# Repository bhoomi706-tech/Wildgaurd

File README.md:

# 🌿 WildGuard IoT System

## 🚀 Overview
WildGuard is an IoT-based smart wildlife monitoring and protection system designed to prevent human-animal conflicts and ensure real-time tracking and surveillance.

---

## 🧠 Features
- 📍 GPS Tracking for location monitoring
- 🎥 ESP32-CAM for live video feed
- 🔴 IR Sensors for obstacle/animal detection
- 📡 RFID for identification
- 🚗 Motor Control using TB6612 Driver
- ⚡ Efficient Power Management (12V → 5V → 3.3V)

---

## 🧩 Components Used
- ESP32
- ESP32-CAM
- Neo-6M GPS Module
- RFID RC522
- IR Sensors
- TB6612 Motor Driver
- 12V DC Motors
- Buck Converter (LM2596)
- AMS1117 Voltage Regulator

---

## 🔌 System Architecture
- 12V supply powers motors
- Buck converter steps down to 5V
- AMS1117 regulates 3.3V for ESP32 and sensors
- ESP32 acts as the main controller

---

## 🛠️ Technologies
- Embedded Systems
- IoT
- PCB Design (KiCad)
- Wireless Communication

---

## 📂 Project Structure

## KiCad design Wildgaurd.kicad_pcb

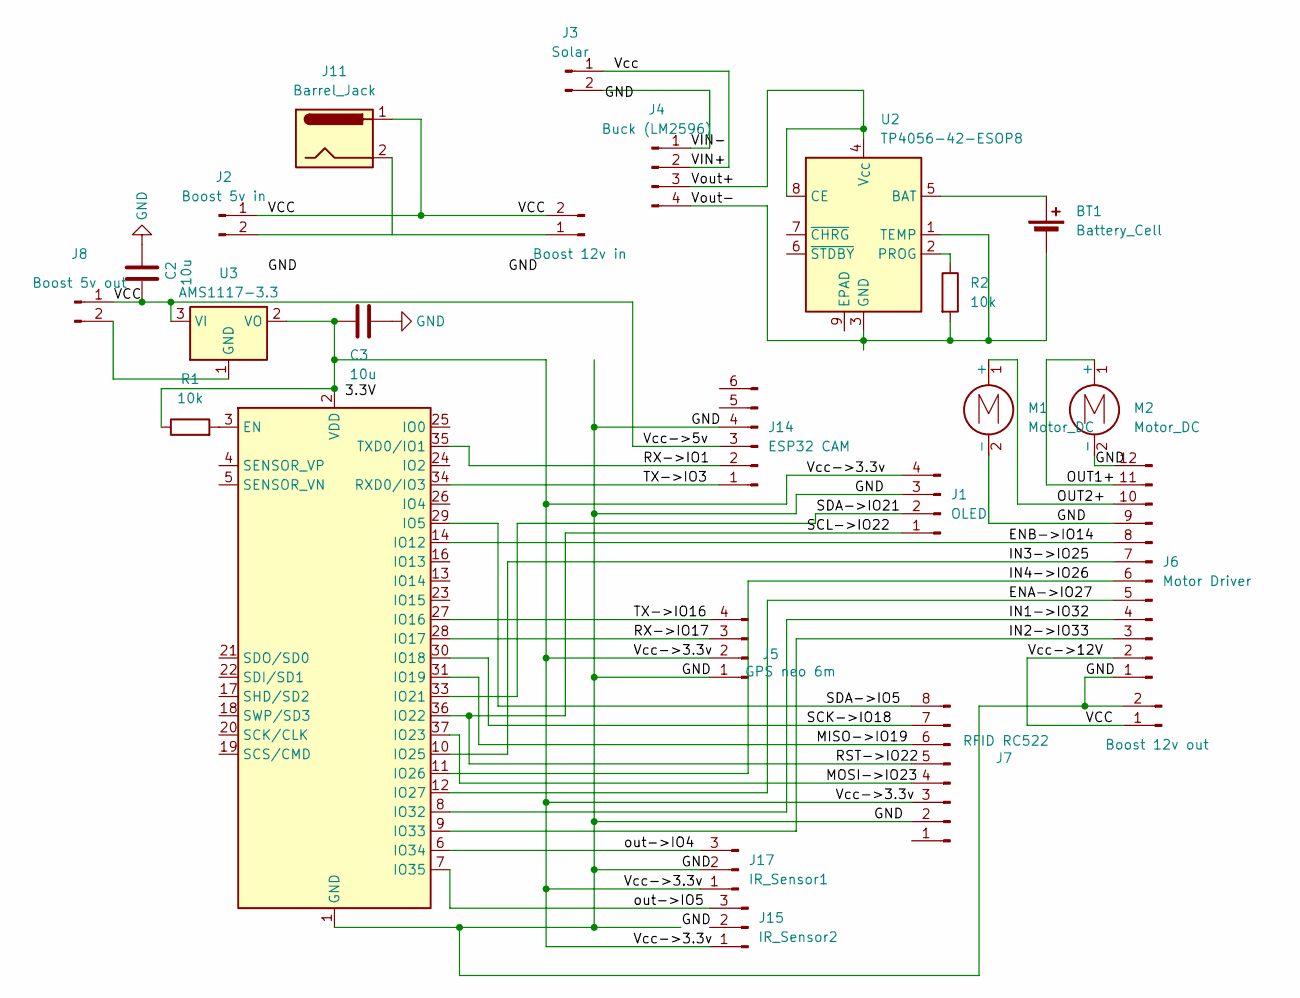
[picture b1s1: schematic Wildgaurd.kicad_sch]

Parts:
BT1: Battery_Cell; BatteryHolder_Keystone_1042_1x18650
C2, C3: 10u; C_0805_2012Metric
J1: OLED; PinHeader_1x04_P2.54mm_Vertical
J2: Boost 5v in; PinHeader_1x02_P2.54mm_Vertical
J3: Solar; PinHeader_1x02_P2.54mm_Vertical
J4: Buck (LM2596); PinHeader_1x04_P2.54mm_Vertical
J5: GPS neo 6m; PinHeader_1x04_P2.54mm_Vertical
J6: Motor Driver; PinHeader_1x12_P2.54mm_Vertical
J7: RFID RC522; PinHeader_1x08_P2.54mm_Vertical
J8: Boost 5v out; PinHeader_1x02_P2.54mm_Vertical
J9: Boost 12v in; PinHeader_1x02_P2.54mm_Vertical
J10: Boost 12v out; PinHeader_1x02_P2.54mm_Vertical
J11: Barrel_Jack; BarrelJack_Horizontal
J14: ESP32 CAM; PinHeader_1x06_P2.54mm_Vertical
J15: IR_Sensor2; PinHeader_1x03_P2.54mm_Vertical
J17: IR_Sensor1; PinHeader_1x03_P2.54mm_Vertical
M1, M2: Motor_DC; TerminalBlock_MaiXu_MX126-5.0-02P_1x02_P5.00mm
R1, R2: 10k; R_0815_2038Metric
U1: ESP32-WROOM-32
U2: TP4056-42-ESOP8; SOIC-8-1EP_3.9x4.9mm_P1.27mm_EP2.41x3.3mm_ThermalVias
U3: AMS1117-3.3; SOT-223-3_TabPin2

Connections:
/ENA->IO27: J6.5, U1.12 (IO27)
/ENB->IO14: J6.8, U1.14 (IO12)
/IN1->IO32: J6.4, U1.8 (IO32)
/IN2->IO33: J6.3, U1.9 (IO33)
/IN3->IO25: J6.7, U1.10 (IO25)
/IN4->IO26: J6.6, U1.11 (IO26)
/MISO->IO19: J7.6, U1.31 (IO19)
/MOSI->IO23: J7.4, U1.37 (IO23)
/OUT1+: J6.11, M2.1 (+)
/OUT2+: J6.10, M1.1 (+)
/RST->IO22: J1.1, J7.5, U1.36 (IO22)
/RX->IO1: J14.2, U1.35 (TXD0/IO1)
/RX->IO17: J5.3, U1.28 (IO17)
/SCK->IO18: J7.7, U1.30 (IO18)
/SDA->IO5: J7.8, U1.29 (IO5)
/SDA->IO21: J1.2, U1.33 (IO21)
/TX->IO3: J14.1, U1.34 (RXD0/IO3)
/TX->IO16: J5.4, U1.27 (IO16)
/VCC: C2.2, J2.1, J6.2, J8.1, J9.2, J10.1, J11.1, J14.3, U3.3 (VI)
/VIN+: J3.1, J4.2
/VIN-: J3.2, J4.1
/Vcc->3.3v: C3.2, J1.4, J5.2, J7.3, J15.1, J17.1, R1.1, U1.2 (VDD), U3.2 (VO)
/Vout+: J4.3, U2.4 (V_{CC}), U2.8 (CE)
/Vout-: BT1.2 (-), J4.4, R2.2, U2.1 (TEMP), U2.3 (GND)
/out->IO4: J17.3, U1.6 (IO34)
/out->IO5: J15.3, U1.7 (IO35)
GND: C2.1, C3.1, J1.3, J5.1, J6.1, J6.9, J6.12, J7.2, J10.2, J14.4, J17.2, M1.2 (-), M2.2 (-), U1.1 (GND), U1.15 (GND), U1.38 (GND), U1.39 (GND)
unnamed: BT1.1 (+), U2.5 (BAT)
unnamed: J2.2, J9.1
unnamed: J8.2, U3.1 (GND)
unnamed: R1.2, U1.3 (EN)
unnamed: R2.1, U2.2 (PROG)

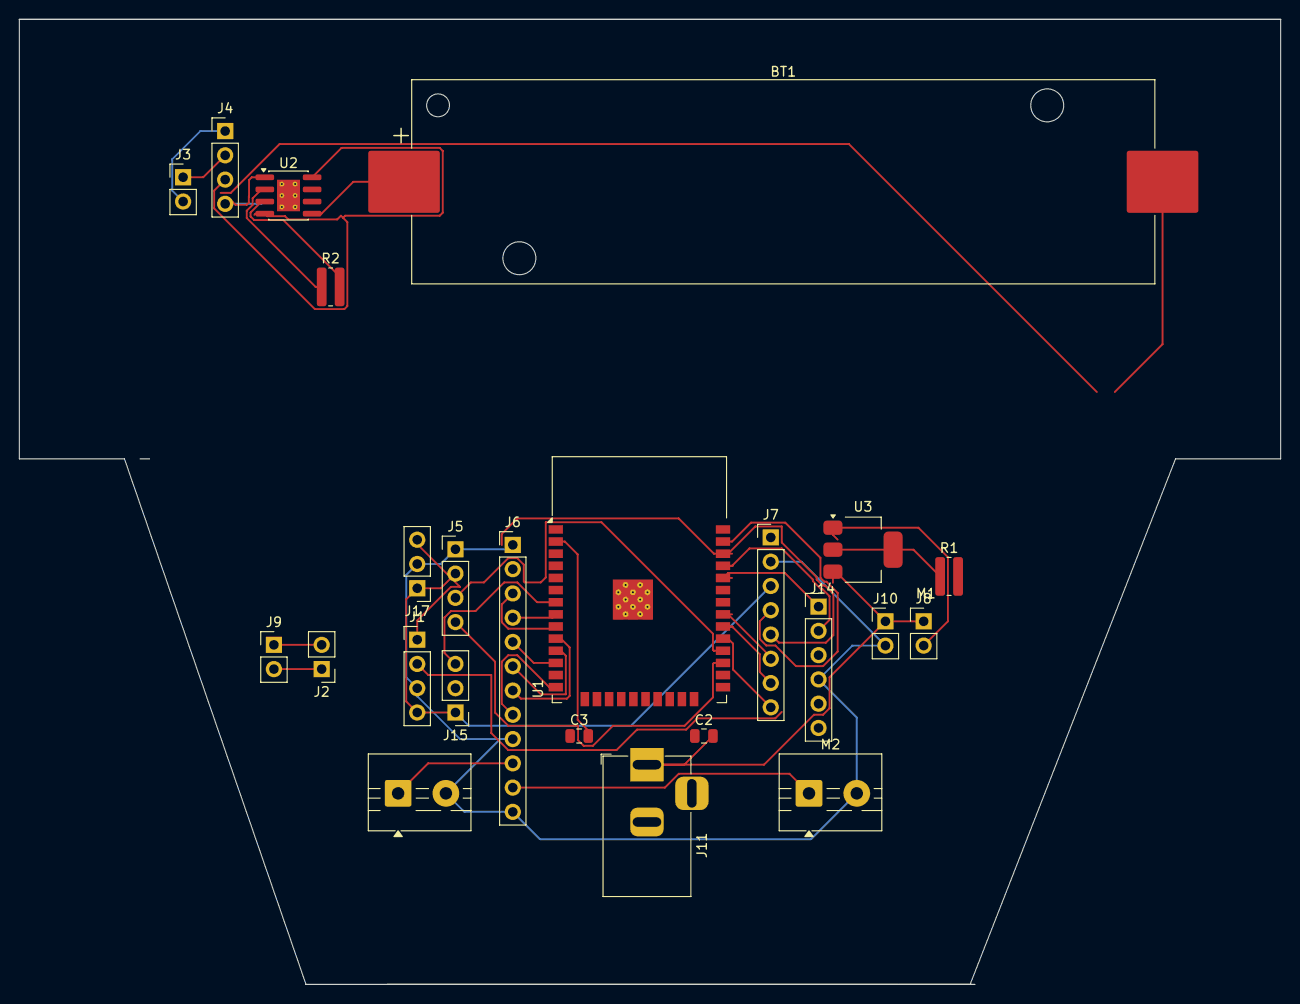
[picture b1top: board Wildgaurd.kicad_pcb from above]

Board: 2 copper layers, 132.0 x 101.0 mm, 24 parts (0 on the bottom side), 32 nets.

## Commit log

2026-04-11 Clean repo: removed unnecessary files
2026-04-11 Add README.md for WildGuard IoT System
    Added detailed project overview, features, components, system architecture, and technologies used in the WildGuard IoT System.
